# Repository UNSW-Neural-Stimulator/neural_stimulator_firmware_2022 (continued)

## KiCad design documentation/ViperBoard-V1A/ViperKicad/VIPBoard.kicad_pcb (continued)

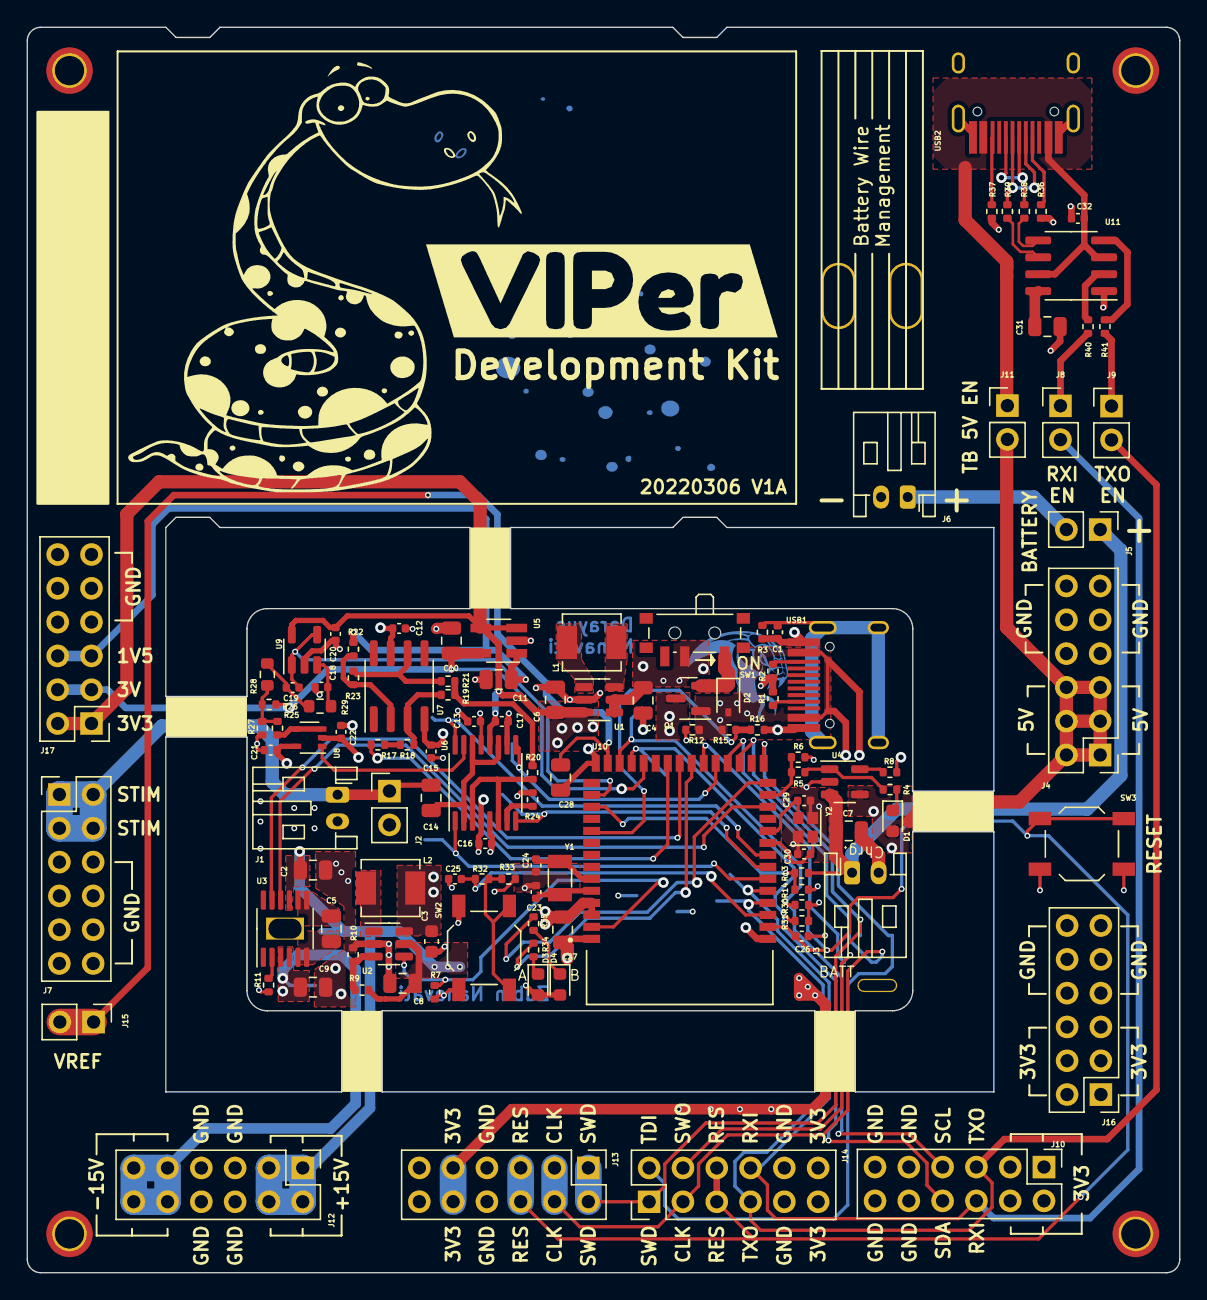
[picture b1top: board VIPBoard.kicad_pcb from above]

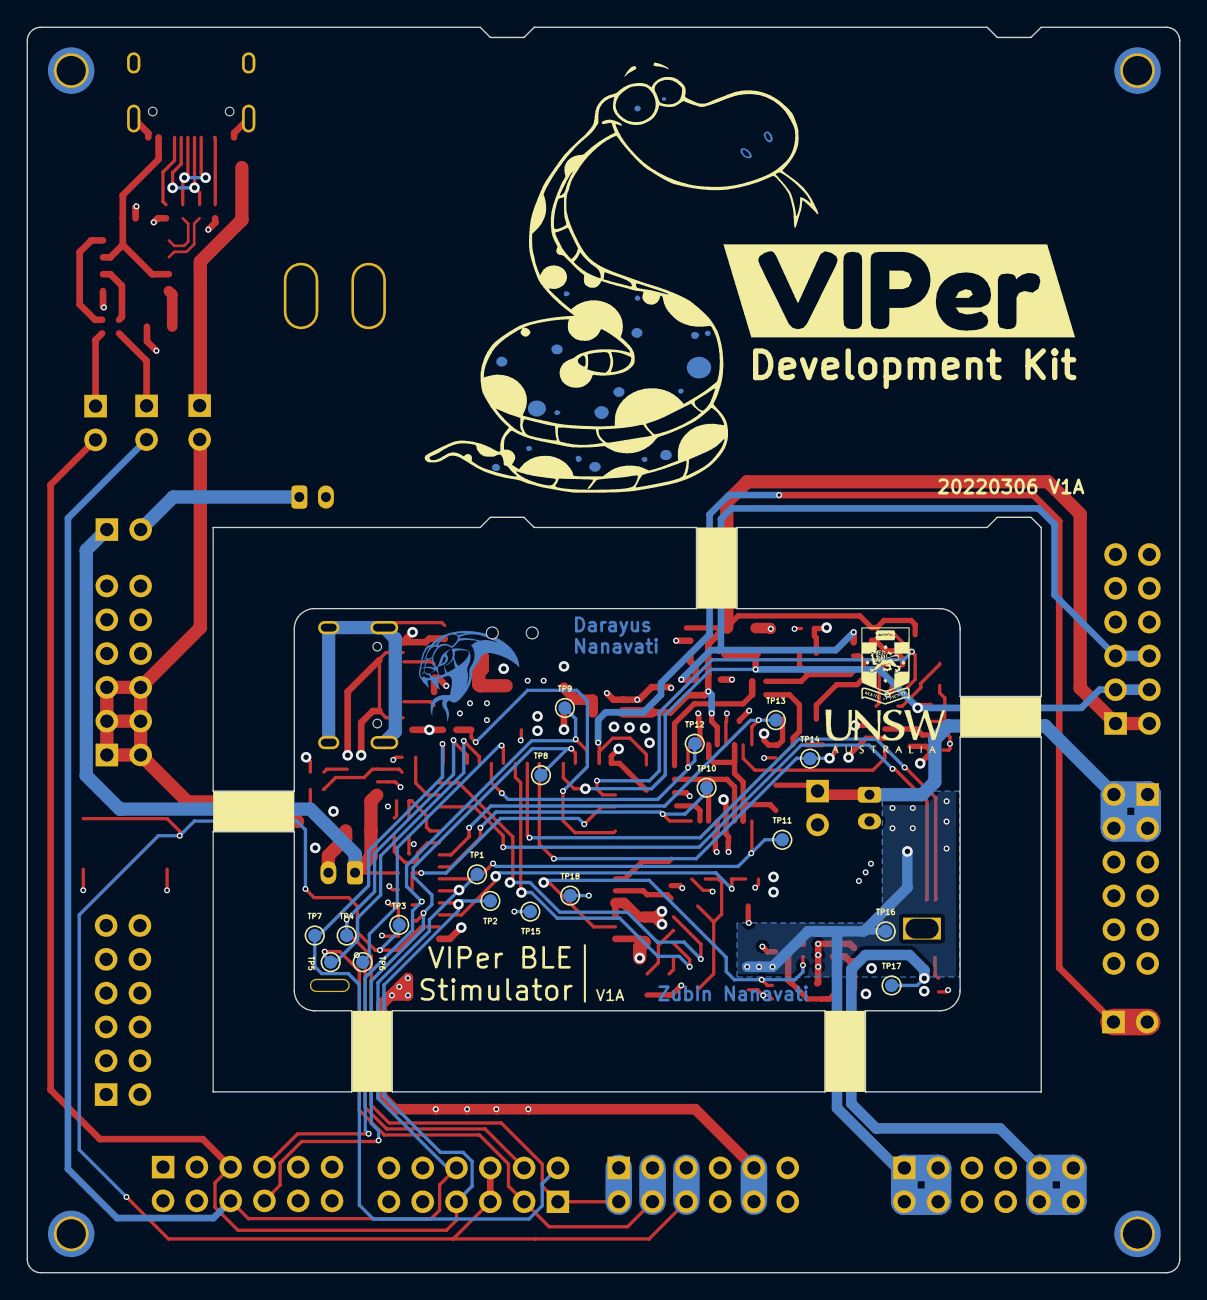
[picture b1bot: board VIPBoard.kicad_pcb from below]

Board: 4 copper layers, 86.6 x 93.6 mm, 135 parts (19 on the bottom side), 82 nets.

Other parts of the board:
kibuzzard-62244E10, kibuzzard-62244E10#2: G***; kibuzzard-62244E10

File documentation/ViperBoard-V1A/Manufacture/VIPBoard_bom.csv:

Comment,Designator,Footprint,LCSC
10n,C1,Capacitor_SMD:C_0402_1005Metric,C15195
100n,"C12,C13,C15,C16,C17,C20,C21,C22,C25,C26,C32",Capacitor_SMD:C_0402_1005Metric,C307331
47p,C18,Capacitor_SMD:C_0402_1005Metric,C1567
100p,C19,Capacitor_SMD:C_0402_1005Metric,C1546
10u,"C2,C7,C8,C9,C14,C27",Capacitor_SMD:C_0805_2012Metric,C440198
22p,"C23,C24",Capacitor_SMD:C_0402_1005Metric,C1555
10p,"C29,C30",Capacitor_SMD:C_0402_1005Metric,C32949
4.7u,C3,Capacitor_SMD:C_0603_1608Metric,C19666
22u,"C4,C6",Capacitor_SMD:C_0805_2012Metric,C45783
1u,"C5,C10,C11,C28,C31",Capacitor_SMD:C_0805_2012Metric,C28323
RED,"D1,D4",LED_SMD:LED_0603_1608Metric,C2286
D_Schottky,D2,Diode_SMD:D_SOD-323,C191023
BLUE,D3,LED_SMD:LED_0603_1608Metric,C72041
JST_PH,"J1,J3,J6",Connector_JST:JST_PH_S2B-PH-K_1x02_P2.00mm_Horizontal,C16965
COMS,J10,Connector_PinHeader_2.54mm:PinHeader_2x06_P2.54mm_Vertical,C124388
EN_TB_5V,J11,Connector_PinHeader_2.54mm:PinHeader_1x02_P2.54mm_Vertical,C492401
DEBUG_KITPROG,J13,Connector_PinHeader_2.54mm:PinHeader_2x06_P2.54mm_Vertical,C124388
DEBUG_FULL,J14,Connector_PinHeader_2.54mm:PinHeader_2x06_P2.54mm_Vertical,C124388
VREF,J15,Connector_PinHeader_2.54mm:PinHeader_1x02_P2.54mm_Vertical,C492401
Conn_02x06_Odd_Even,"J4,J7,J12,J16,J17",Connector_PinHeader_2.54mm:PinHeader_2x06_P2.54mm_Vertical,C124388
I_Sense,J5,Connector_PinHeader_2.54mm:PinHeader_1x02_P2.54mm_Vertical,C492401
DIS_TB_RXI,J8,Connector_PinHeader_2.54mm:PinHeader_1x02_P2.54mm_Vertical,C492401
DIS_TB_TXO,J9,Connector_PinHeader_2.54mm:PinHeader_1x02_P2.54mm_Vertical,C492401
10u,"L1,L2",Custom_Footprints:4.4x4.2x2mm Power Inductor,C177242
AO3401A,Q1,Package_TO_SOT_SMD:SOT-23,C15127
5K11,"R1,R2,R36,R37",Resistor_SMD:R_0402_1005Metric,C25905
56k,R10,Resistor_SMD:R_0402_1005Metric,C25796
400R 0.1%,"R17,R21",Resistor_SMD:R_0402_1005Metric,C317913
25K 0.1%,"R18,R19,R22,R23",Resistor_SMD:R_0402_1005Metric,C136978
50R,R20,Resistor_SMD:R_0402_1005Metric,C25120
20K,R26,Resistor_SMD:R_0402_1005Metric,C25765
24K,R27,Resistor_SMD:R_0402_1005Metric,C25769
62K,R28,Resistor_SMD:R_0603_1608Metric,C23221
36K,R29,Resistor_SMD:R_0603_1608Metric,C23147
100K,"R3,R7,R12,R25",Resistor_SMD:R_0402_1005Metric,C25741
33R,"R38,R39",Resistor_SMD:R_0402_1005Metric,C25105
1K,"R4,R24,R32,R34,R35",Resistor_SMD:R_0402_1005Metric,C11702
10K,"R5,R13,R15,R33",Resistor_SMD:R_0402_1005Metric,C25744
15K,"R6,R14,R16",Resistor_SMD:R_0402_1005Metric,C25756
4K7,"R8,R11,R30,R31,R40,R41",Resistor_SMD:R_0402_1005Metric,C25900
1M,R9,Resistor_SMD:R_0402_1005Metric,C26083
SW_SPST,SW1,Button_Switch_SMD:SW_SPDT_PCM12,C431540
SW_USR,SW2,Button_Switch_SMD:SW_SPST_TL3342,C318884
SW_RESET,SW3,Button_Switch_SMD:SW_SPST_TL3342,C318884
HRO-TYPE-C-31-M-12,"USB1,USB2",HRO-TYPE-C-31-M-12:HRO-TYPE-C-31-M-12-HandSoldering,C167321
WCO 32.768KHz,Y1,Custom_Footprints:Crystal_SMD_3215-2Pin_3.2x1.5mm,C32346

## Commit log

2022-03-18 New: Fixed .gitignore
    Replaced .gitignore with .gitoignore from old repo
2022-03-18 Updated README
    Added most of the necessary content to the README.md file
2022-03-20 Add weekly tasks and 2021 code
2022-03-20 Added DAC task from week 4
2022-03-20 Added blinking LED task
2022-03-20 Added Firmware Code
2022-03-20 add biphasic wave
2022-03-25 Create biphasic wave program
2022-03-25 Improve commenting
2022-04-03 Added code for task
2022-04-08 Add switches example
2022-04-14 Add documentation and use all 4 switches
2022-04-14 Add BLE test, changes the LEDS on board
2022-04-14 Add bluetooth functionality to switches
2022-04-27 Add documentation and trim whitepace from cm4
2022-06-02 simplification
2022-06-14 incorrectMagnitude
2022-06-21 buffered settings
2022-06-21 buffered dac correct branch
2022-06-27 working copy
2022-07-04 Add UARt and tester projects
2022-07-05 Created BLE_Send_Receive project
2022-07-06 Add BLEREad test and UART test
2022-07-06 Improve error messages
2022-07-06 Add NSTIM
2022-07-06 Add notification example
2022-07-07 Add dc switch timing diagram
2022-07-07 Add curr <-> vdac conversion
2022-07-07 Add burst and pulse counters
2022-07-07 Missed adding firmware, add, burst and pulse counters
2022-07-07 Add DC pulse counter
2022-07-07 Add command and BLE characteristic spreadsheet
2022-07-07 Improve BLE characteristic details
2022-07-11 Add other write commands
2022-07-13 Added remaining read characteristics
2022-07-13 Added BLE read characteristics + made attempt to fix switches
2022-07-14 commit to push/code still working
2022-07-15 Fix type bugs
2022-07-18 Add more reads
2022-07-18 Convert incoming uint32 to float
2022-07-18 Change conversions
2022-07-18 adjust conversion
2022-07-18 Fix conversion
2022-07-18 Remove anodic/cathodic check
2022-07-18 fix anodic check
2022-07-18 Fix dc mode
2022-07-18 Add adc to firmware
2022-07-20 Add adc task
2022-07-20 Add build to gitignore
2022-07-20 keeps excluding pdl for adc
2022-07-20 Merge
2022-07-20 added adc pdl file
2022-07-20 Aayush did not do this
2022-07-20 Fixing .gitignore
2022-07-20 ADC changes
2022-07-25 Fix burst pulse counter
2022-07-27 Added ADC_Calibration file
2022-07-27 Fix switches
2022-07-27 Add compliance check
2022-07-27 Fix compliance check
2022-07-27 Compliance check using wrong value
2022-08-10 Fix dc sloping
2022-08-10 Fix ramping
2022-08-10 Put dac update before switches
2022-08-10 Add shorting
2022-08-10 Add shorting for interphase
2022-08-10 Add in ADCcallback and fix
2022-09-20 Test high low duty cycle, add complete pulse stopping
2022-09-21 Added new linear equation
2022-09-27 Add notify error functionality
2022-09-28 Completed Howland rails task + made attempt at ADC impedance check
2022-10-04 Wait for impedance to finish
2022-10-04 Add start after compliance
2022-10-04 shift impedance start
2022-10-05 Add notify after subscription
2022-10-05 Add printing for notify
2022-10-05 Fix notify
2022-10-05 Add commenting to remove testing section later
2022-10-10 Add impedance check
2022-10-12 Fixed commands to set 0 currents to V0 instead of whats calculated by CURR_TO_VDAC (ensures zero current)
2022-10-14 Push up nice impedance check
2022-10-14 Set vdac value to V0 upon 0 current being entered
2022-10-21 Add notify woohoo it works. TODO: return 16 bit int not 32 bit float
2022-10-21 Pack 16 bit integers not floats
2022-10-24 Impedance check done
2022-10-28 Modified impedance check to notify software when compliance is broken
2022-10-28 Stop stimulation if we hit compliance during stim
2022-10-31 Compliance check at end of AC wave and do DC check
2022-11-12 Add nstim location hint
2023-01-11 Adjustment to DC impedance check
2023-02-16 Take hard coded values out
2024-01-08 Fixed dc impedance check + added neg polarity for dc
